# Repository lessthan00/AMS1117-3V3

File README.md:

# AMS1117-3V3  borad change from HT7333
  
[AMS1117-3V3](https://www.jlc-smt.com/lcsc/detail?componentCode=C5120765)  
LDO  
  
VIN 18V  
VOUT 3.3V  
IOUT 1A  
package SOT-223  
IQ 12mA  
VD 1.4V@1A  
  
引脚引脚定义  
  
1 GND  
2 VOUT  
3 VIN  

输入TVS 改为SMAJ18CA
  
## HT7333  
  
[HT7333](https://item.szlcsc.com/323851.html?fromZone=s_s__%2522HT7333%2522&spm=sc.gb.xh2.zy.n___sc.hm.hd.ss&lcsc_vid=EwQKBQVXRFYIBQVTR1JbVFcAFgRYUl0AFFNZVAEARVQxVlNSQVZWVVFfRVBZXzsOAxUeFF5JWBYZEEoEHg8JSQcJGk4%3D)  
  
LDO  
  
VIN 12V  
VOUT 3.3V  
IOUT 250mA  
package SOT-89-3  
IQ 3uA  
VD 90mV@40mA  
  
引脚定义  
  
1 GND  
2 VIN  
3 VOUT  
  
所以使用kciad 里面的 Regulator_Generic_GND_IN_OUT 生成符号  
  
封装采用PCM_Package_TO_SOT_SMD_AKL:SOT-89-3, 已确认封装焊盘顺序定义无误  
  
## TLV70450DBVR  
  
[TLV70450DBVR](https://www.jlc-smt.com/lcsc/detail?componentCode=C91672)  
VIN 24V  
VOUT 5V  
IOUT 150mA  
IQ 4.5uA  
VD 1.1V@100mA  
package SOT-23-5  
  
1-GND  
2-IN  
3-OUT  
4-NC  
5-NC  
  
这样的封装的引脚定义是很少的,基本上只有TLV70450DBVR,甚至需要自己绘制封装...

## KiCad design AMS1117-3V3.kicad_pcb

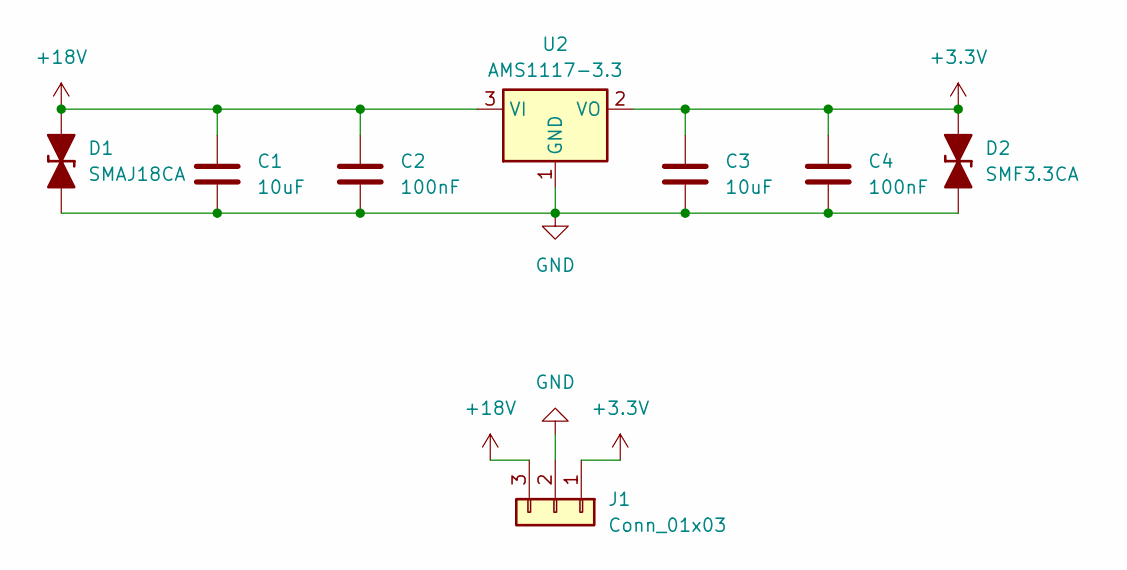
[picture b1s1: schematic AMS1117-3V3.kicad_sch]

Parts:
C1, C3: 10uF; C_1206_3216Metric
C2, C4: 100nF; C_1206_3216Metric
D1: SMAJ18CA; D_SMA_TVS
D2: SMF3.3CA; D_SOD-123F
J1: Conn_01x03; PinHeader_1x03_P2.54mm_Vertical
U2: AMS1117-3.3; SOT-223-3_TabPin2

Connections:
+3.3V: C3.1, C4.1, D2.2 (A), J1.1, U2.2 (VO)
+18V: C1.1, C2.1, D1.2 (A), J1.3, U2.3 (VI)
GND: C1.2, C2.2, C3.2, C4.2, D1.1 (K), D2.1 (K), J1.2, U2.1 (GND)

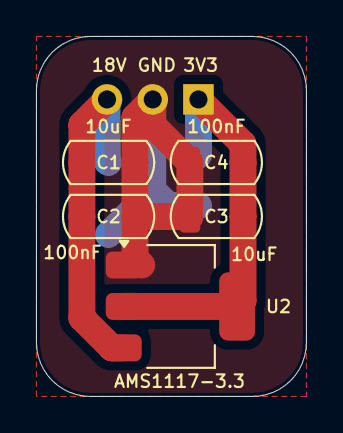
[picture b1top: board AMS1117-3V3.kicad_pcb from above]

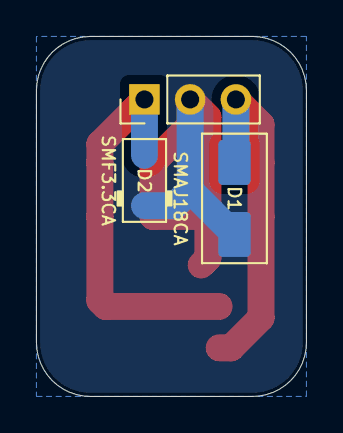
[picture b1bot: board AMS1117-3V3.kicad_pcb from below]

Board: 2 copper layers, 15.0 x 20.0 mm, 8 parts (3 on the bottom side), 3 nets.
